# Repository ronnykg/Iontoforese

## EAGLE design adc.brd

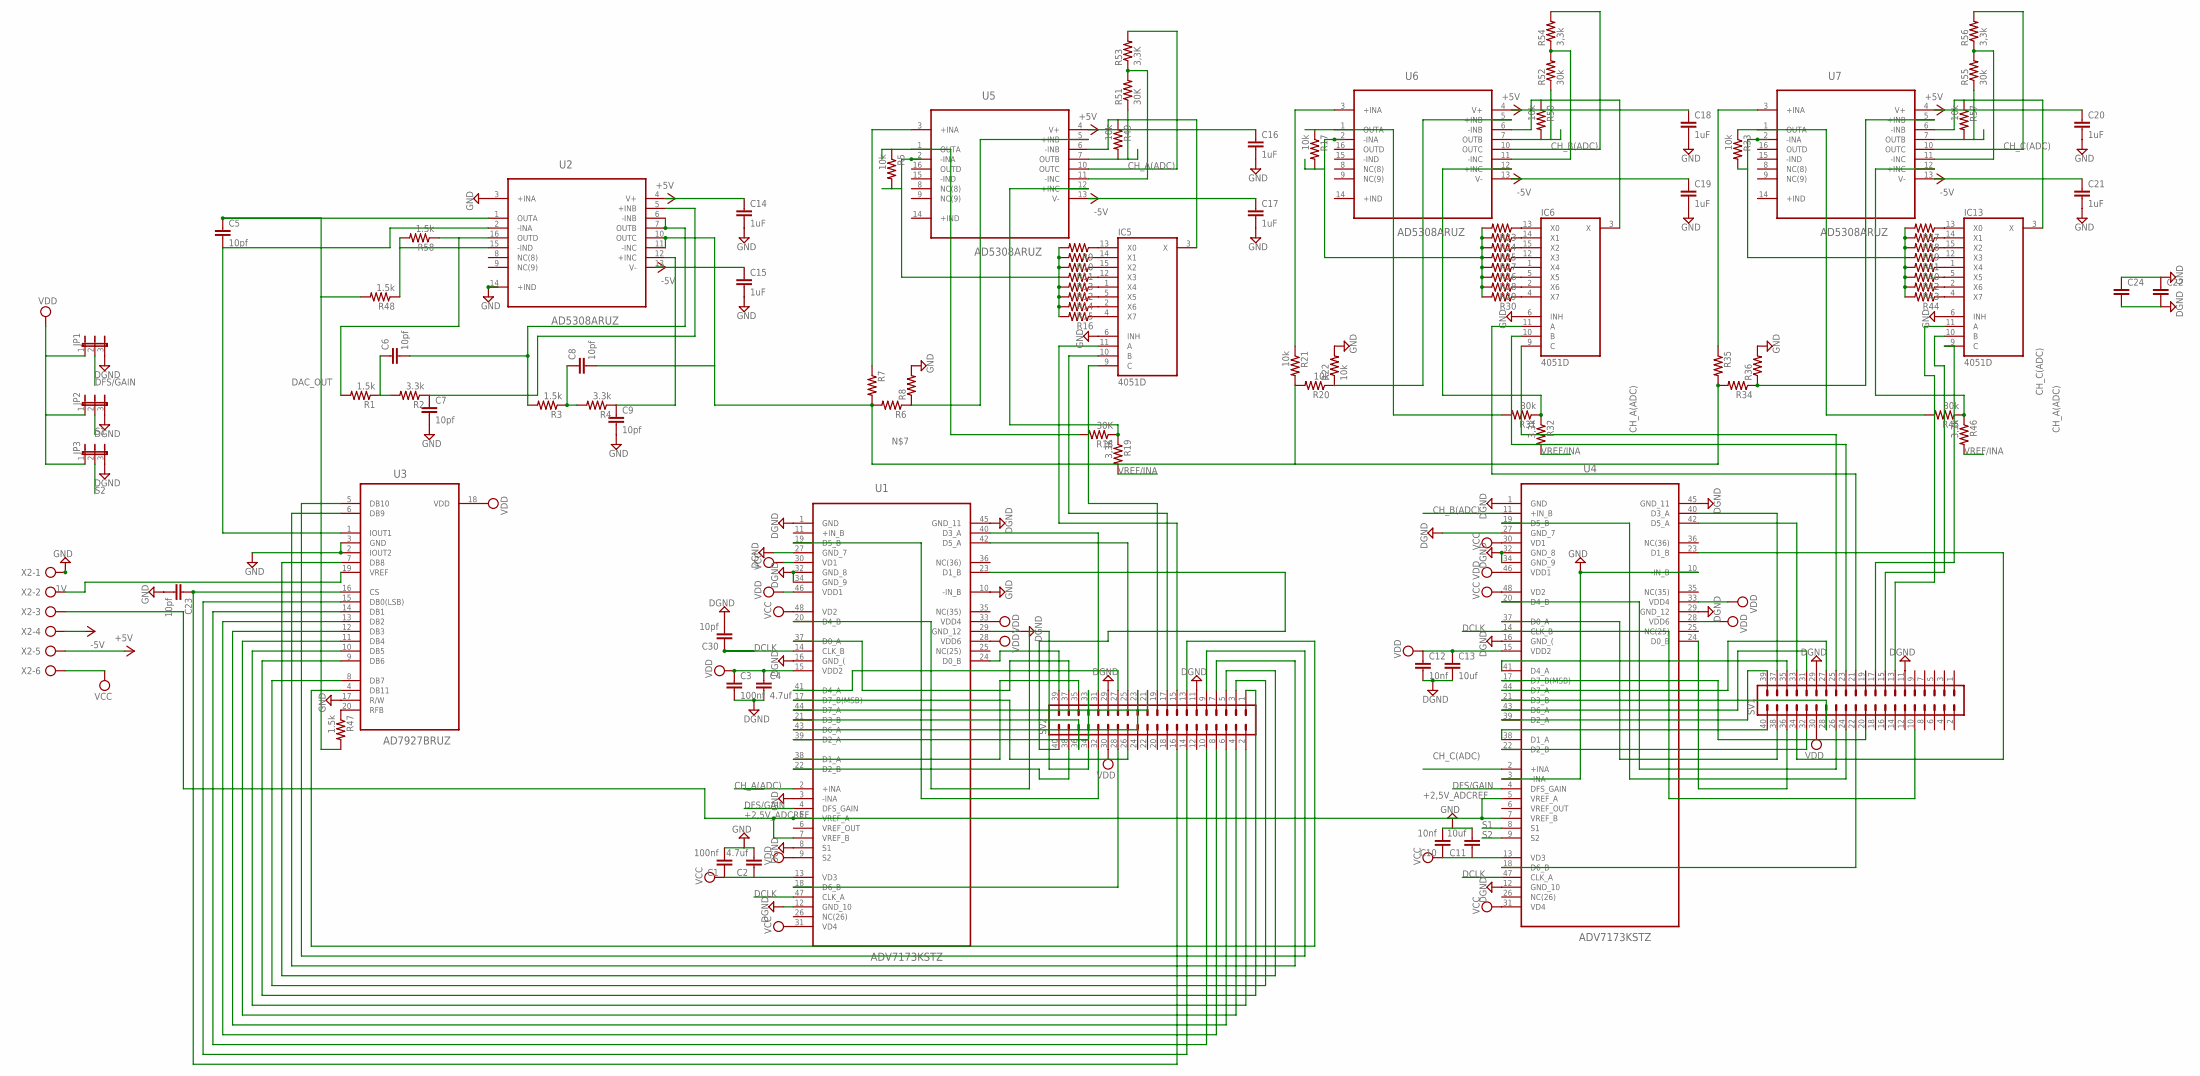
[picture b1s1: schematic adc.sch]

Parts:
C1, C3: 100nf; C0603
C2, C4: 4.7uf; C0603
C5, C6, C7, C8, C9, C23, C30: 10pf; C0603
C10, C12: 10nf; C0603
C11, C13: 10uf; C0603
C14, C15, C16, C17, C18, C19, C20, C21: 1uF; C0603
C22: C2,5-3; C2.5-3
C24: C10/6; C10B6
IC5, IC6, IC13: 4051D; SO16
JP1, JP2, JP3: JP2E; JP2
R1, R3, R47, R48, R58: 1.5k; 0603
R2, R4: 3.3k; 0603
R5, R17, R20, R21, R22, R33, R49, R50, R57: 10k; 0603
R6, R7, R8, R9, R10, R11, R12, R13, R14, R15, R16, R23, R24, R25, R26, R27, R28, R29, R30, R34, R35, R36, R37, R38, R39, R40, R41, R42, R43, R44: RESISTOR0603; 0603
R18, R51: 30K; 0603
R19, R53: 3,3K; 0603
R31, R45, R52, R55: 30k; 0603
R32, R46, R54, R56: 3,3k; 0603
SV1, SV2: MA20-2
U1, U4: ADV7173KSTZ; QFP50P900X900X160-48N
U2, U5, U6, U7: AD5308ARUZ; SOP65P640X120-16N
U3: AD7927BRUZ; SOP65P640X120-20N
X2: AK300/6

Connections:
1V: U3.19 (VREF), X2.2
+2,5V_ADCREF: U1.5 (VREF_A), U1.7 (VREF_B), U4.5 (VREF_A), U4.7 (VREF_B), X2.3
+5V: C14.1, C16.1, C18.1, C20.1, IC5.16 (+5V), IC6.16 (+5V), IC13.16 (+5V), U2.4 (V+), U5.4 (V+), U6.4 (V+), U7.4 (V+), X2.5
+IN_B: U1.11 (+IN_B)
-5V: C15.1, C17.1, C19.1, C21.1, IC5.7 (VEE), IC6.7 (VEE), IC13.7 (VEE), U2.13 (V-), U5.13 (V-), U6.13 (V-), U7.13 (V-), X2.4
CH_A(ADC): R53.2, U1.2 (+INA), U5.10 (OUTC)
CH_B(ADC): R54.2, U4.11 (+IN_B), U6.10 (OUTC)
CH_C(ADC): R56.2, U4.2 (+INA), U7.10 (OUTC)
DAC_OUT: C5.1, R47.2, R48.2, U2.1 (OUTA)
DCLK: C30.1, SV1.10, U1.14 (CLK_B), U1.47 (CLK_A), U4.14 (CLK_B), U4.47 (CLK_A)
DFS/GAIN: JP1.2, U1.4 (DFS_GAIN), U4.4 (DFS_GAIN)
DGND: C3.2, C4.2, C12.2, C13.2, C22.2, C24.2, C30.2, JP1.3, JP2.3, JP3.3, SV1.11, SV1.29, SV2.11, SV2.29, U1.1 (GND), U1.8 (S1), U1.12 (GND_10), U1.16 (GND_(), U1.27 (GND_7), U1.29 (GND_12), U1.32 (GND_8), U1.34 (GND_9), U1.45 (GND_11), U4.1 (GND), U4.12 (GND_10), U4.16 (GND_(), U4.27 (GND_7), U4.29 (GND_12), U4.32 (GND_8), U4.34 (GND_9), U4.45 (GND_11)
GND: C1.2, C2.2, C7.2, C9.2, C10.2, C11.2, C14.2, C15.2, C16.2, C17.2, C18.2, C19.2, C20.2, C21.2, C22.1, C23.2, C24.1, IC5.6 (INH), IC5.8 (GND), IC6.6 (INH), IC6.8 (GND), IC13.6 (INH), IC13.8 (GND), R8.2, R22.2, R36.2, U1.3 (-INA), U1.10 (-IN_B), U2.3 (+INA), U2.14 (+IND), U3.2 (IOUT2), U3.3 (GND), U3.17 (R/W), U4.3 (-INA), U4.10 (-IN_B), X2.1
unnamed: C7.1, R2.1, U2.5 (+INB)
unnamed: C6.1, R1.1, R2.2
unnamed: R48.1, R58.2, U2.15 (-IND)
unnamed: C6.2, R3.2, U2.6 (-INB), U2.7 (OUTB)
unnamed: C9.1, R4.1, U2.12 (+INC)
unnamed: C8.1, R3.1, R4.2
unnamed: C8.2, R6.2, R7.2, R20.2, R21.2, R34.2, R35.2, U2.10 (OUTC), U2.11 (-INC)
unnamed: SV2.31, U1.40 (D3_A)
unnamed: SV2.25, U1.42 (D5_A)
unnamed: SV2.39, U1.24 (D0_B)
unnamed: SV2.32, U1.19 (D5_B)
unnamed: SV2.34, U1.20 (D4_B)
unnamed: SV2.37, U1.37 (D0_A)
unnamed: SV2.27, U1.41 (D4_A)
unnamed: SV2.21, U1.44 (D7_A)
unnamed: SV2.36, U1.21 (D3_B)
unnamed: SV2.23, U1.43 (D6_A)
unnamed: SV2.33, U1.39 (D2_A)
unnamed: SV2.35, U1.38 (D1_A)
unnamed: SV2.38, U1.22 (D2_B)
unnamed: SV2.28, U1.18 (D6_B)
unnamed: SV2.26, U1.17 (D7_B(MSB))
unnamed: SV2.13, U3.4 (DB11)
unnamed: SV2.40, U1.23 (D1_B)
unnamed: SV2.9, U3.5 (DB10)
unnamed: SV2.7, U3.6 (DB9)
unnamed: SV2.5, U3.7 (DB8)
unnamed: SV2.3, U3.8 (DB7)
unnamed: SV2.1, U3.9 (DB6)
unnamed: SV2.2, U3.10 (DB5)
unnamed: SV2.4, U3.11 (DB4)
unnamed: SV2.6, U3.12 (DB3)
unnamed: SV2.8, U3.13 (DB2)
unnamed: SV2.10, U3.14 (DB1)
unnamed: SV2.14, U3.15 (DB0(LSB))
unnamed: SV1.38, U4.37 (D0_A)
unnamed: IC5.13 (X0), R9.1
unnamed: IC5.14 (X1), R10.1
unnamed: IC5.15 (X2), R11.1
unnamed: IC5.1 (X4), R12.1
unnamed: IC5.12 (X3), R13.1
unnamed: IC5.5 (X5), R14.1
unnamed: IC5.2 (X6), R15.1
unnamed: IC5.4 (X7), R16.1
unnamed: IC6.13 (X0), R23.1
unnamed: IC6.14 (X1), R24.1
unnamed: R17.2, R23.2, R24.2, R25.2, R26.2, R27.2, R28.2, R29.2, R30.2, U6.2 (-INA)
unnamed: R5.2, R9.2, R10.2, R11.2, R12.2, R13.2, R14.2, R15.2, R16.2, U5.2 (-INA)
unnamed: R18.1, R19.1, U5.12 (+INC)
unnamed: R49.2, R51.1, U5.7 (OUTB)
unnamed: IC6.15 (X2), R25.1
unnamed: IC6.1 (X4), R26.1
unnamed: IC6.12 (X3), R27.1
unnamed: IC6.5 (X5), R28.1
unnamed: IC6.2 (X6), R29.1
unnamed: IC6.4 (X7), R30.1
unnamed: R52.2, R54.1, U6.11 (-INC)
unnamed: R33.1, R45.2, U7.1 (OUTA)
unnamed: IC13.3 (X), R57.1, U7.6 (-INB)
unnamed: IC13.13 (X0), R37.1
unnamed: IC13.14 (X1), R38.1
unnamed: IC13.15 (X2), R39.1
unnamed: IC13.1 (X4), R40.1
unnamed: IC13.12 (X3), R41.1
unnamed: IC13.5 (X5), R42.1
unnamed: IC13.2 (X6), R43.1
unnamed: IC13.4 (X7), R44.1
unnamed: R34.1, R36.1, U7.5 (+INB)
unnamed: R6.1, R8.1, U5.5 (+INB)
unnamed: R20.1, R22.1, U6.5 (+INB)
unnamed: R7.1, U5.3 (+INA)
unnamed: SV1.40, U4.38 (D1_A)
unnamed: SV1.39, U4.39 (D2_A)
unnamed: SV1.36, U4.24 (D0_B)
unnamed: SV1.24, U4.19 (D5_B)
unnamed: SV1.26, U4.20 (D4_B)
unnamed: SV1.37, U4.40 (D3_A)
unnamed: SV1.35, U4.41 (D4_A)
unnamed: SV1.33, U4.42 (D5_A)
unnamed: SV1.28, U4.21 (D3_B)
unnamed: SV1.31, U4.43 (D6_A)
unnamed: SV1.27, U4.44 (D7_A)
unnamed: SV1.32, U4.22 (D2_B)
unnamed: SV1.22, U4.18 (D6_B)
unnamed: SV1.20, U4.17 (D7_B(MSB))
unnamed: SV1.34, U4.23 (D1_B)
unnamed: IC5.9 (C), SV2.19
unnamed: IC5.10 (B), SV2.17
unnamed: IC13.9 (C), SV1.17
unnamed: IC13.10 (B), SV1.15
unnamed: IC13.11 (A), SV1.13
unnamed: IC6.9 (C), SV1.25
unnamed: IC6.10 (B), SV1.23
unnamed: IC6.11 (A), SV1.21
unnamed: IC5.3 (X), R49.1, U5.6 (-INB)
unnamed: R31.1, R32.1, U6.12 (+INC)
unnamed: R33.2, R37.2, R38.2, R39.2, R40.2, R41.2, R42.2, R43.2, R44.2, U7.2 (-INA)
unnamed: C5.2, U2.2 (-INA), U3.1 (IOUT1)
unnamed: R45.1, R46.1, U7.12 (+INC)
unnamed: R5.1, R18.2, U5.1 (OUTA)
unnamed: R35.1, U7.3 (+INA)
unnamed: R21.1, U6.3 (+INA)
unnamed: R47.1, U3.20 (RFB)
unnamed: IC5.11 (A), SV2.15
unnamed: C23.1, SV2.16, U3.16 (CS)
unnamed: R55.2, R56.1, U7.11 (-INC)
unnamed: R51.2, R53.1, U5.11 (-INC)
unnamed: R55.1, R57.2, U7.7 (OUTB)
unnamed: R17.1, R31.2, U6.1 (OUTA)
unnamed: R50.2, R52.1, U6.7 (OUTB)
unnamed: IC6.3 (X), R50.1, U6.6 (-INB)
unnamed: R1.2, R58.1, U2.16 (OUTD)
S1: JP2.2, U4.8 (S1)
S2: JP3.2, U4.9 (S2)
VCC: C1.1, C2.1, C10.1, C11.1, U1.13 (VD3), U1.30 (VD1), U1.31 (VD4), U1.48 (VD2), U4.13 (VD3), U4.30 (VD1), U4.31 (VD4), U4.48 (VD2), X2.6
VDD: C3.1, C4.1, C12.1, C13.1, JP1.1, JP2.1, JP3.1, SV1.30, SV2.30, U1.9 (S2), U1.15 (VDD2), U1.28 (VDD6), U1.33 (VDD4), U1.46 (VDD1), U3.18 (VDD), U4.15 (VDD2), U4.28 (VDD6), U4.33 (VDD4), U4.46 (VDD1)
VEE: IC5.7 (VEE), IC6.7 (VEE), IC13.7 (VEE)
VREF/INA: R19.2, R32.2, R46.2

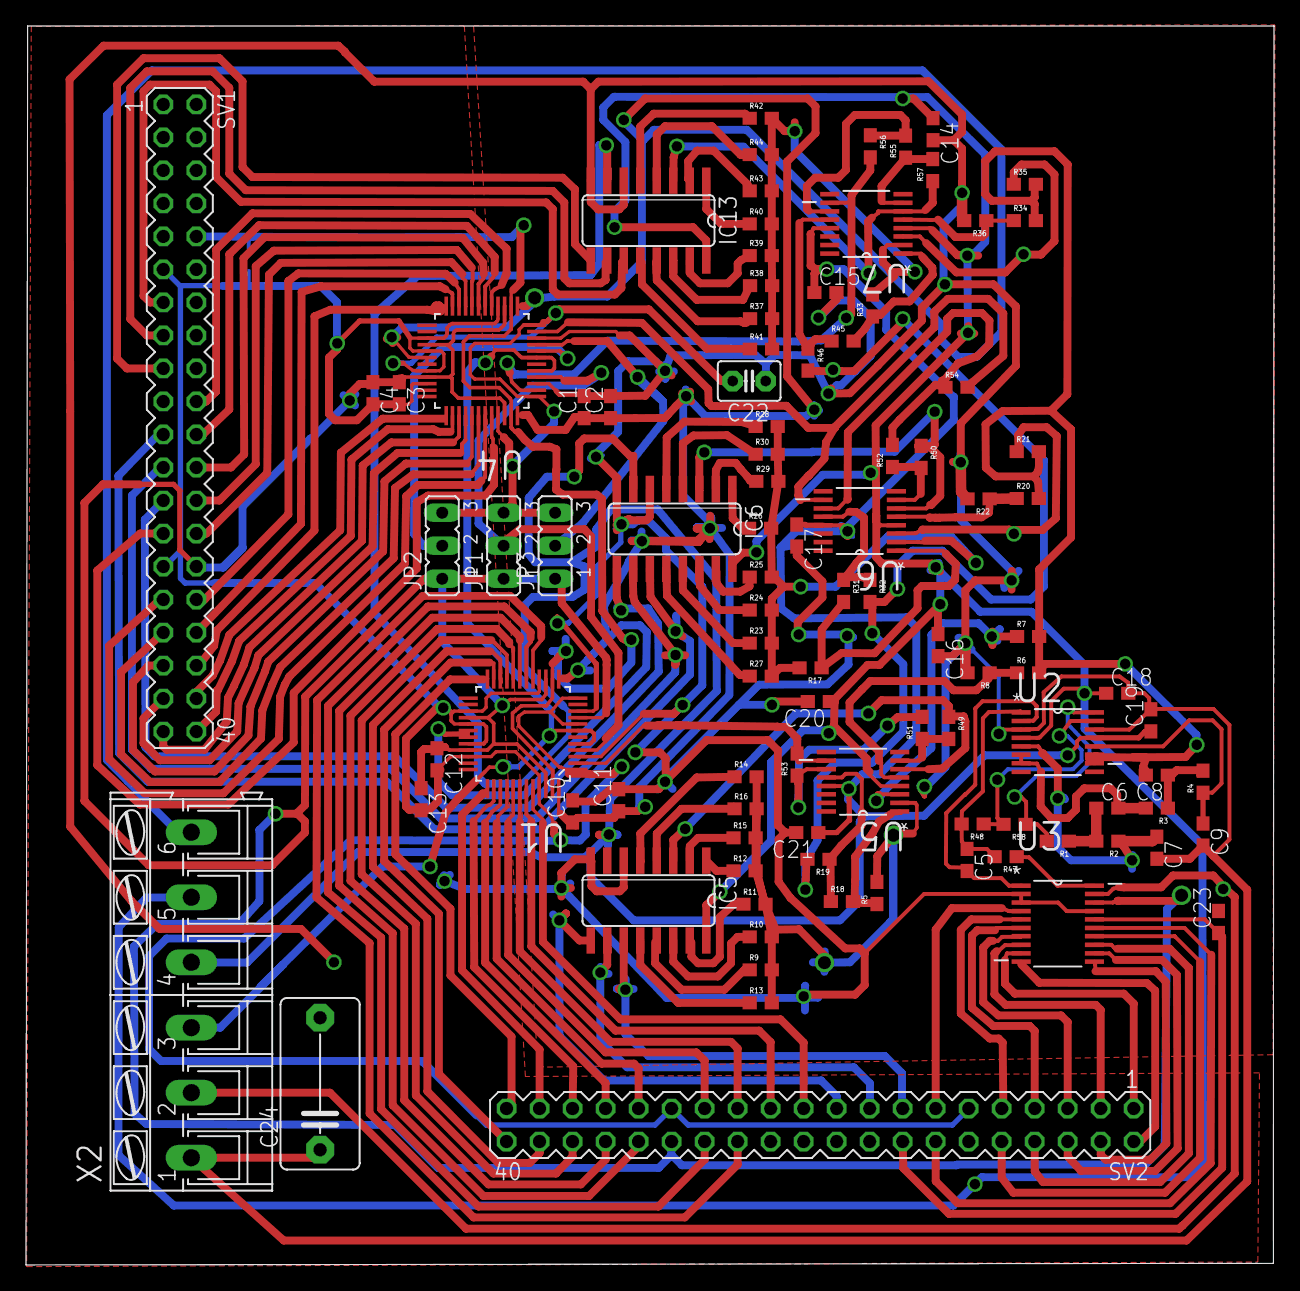
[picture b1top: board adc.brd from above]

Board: 2 copper layers, 96.0 x 95.3 mm, 99 parts (1 on the bottom side), 130 nets.

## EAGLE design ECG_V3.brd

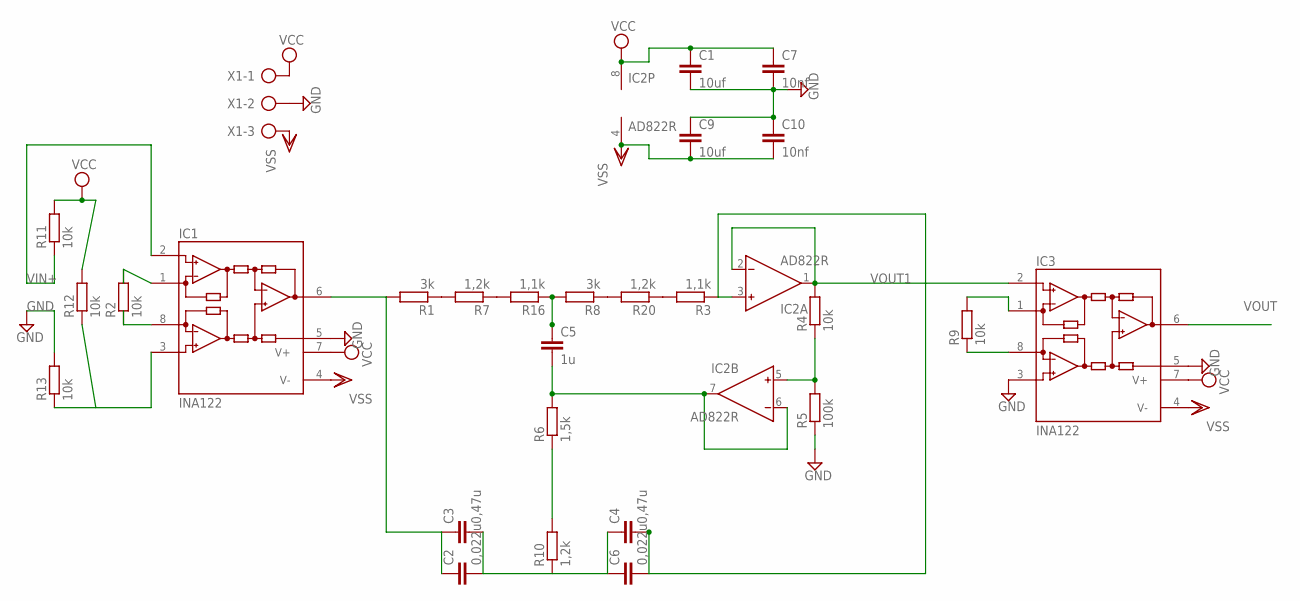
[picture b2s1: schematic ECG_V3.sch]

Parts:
C1, C9: 10uf; C0603
C2, C6: 0,022u; C0603
C3, C4: 0,47u; C0603
C5: 1u; C0603
C7, C10: 10nf; C0603
IC1, IC3: INA122; SO08
IC2: AD822R; SO8
R1, R8: 3k; R0603
R2, R4, R9, R11, R12, R13: 10k; R0603
R3, R16: 1,1k; R0603
R5: 100k; R0603
R6: 1,5k; R0603
R7, R10, R20: 1,2k; R0603
X1: AK300/3

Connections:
GND: C1.2, C7.2, C9.1, C10.1, IC1.5 (REF), IC3.3 (+IN), IC3.5 (REF), R5.1, R13.2, X1.2
unnamed: IC3.1 (RG), R9.2
unnamed: IC3.8 (RG), R9.1
unnamed: IC1.1 (RG), R2.2
unnamed: IC1.8 (RG), R2.1
unnamed: R1.1, R7.2
unnamed: R7.1, R16.2
unnamed: R3.2, R20.1
unnamed: IC2.5 (IN+), R4.1, R5.2
unnamed: R8.1, R20.2
unnamed: C5.2, IC2.6 (IN-), IC2.7 (OUT), R6.2
unnamed: C5.1, R8.2, R16.1
unnamed: IC1.3 (+IN), R12.1, R13.1
unnamed: R6.1, R10.2
unnamed: C2.2, C3.2, C4.1, C6.1, R10.1
unnamed: C2.1, C3.1, IC1.6 (OUT), R1.2
unnamed: C4.2, C6.2, IC2.3 (IN+), R3.1
VCC: C1.1, C7.1, IC1.7 (V+), IC2.8 (V+), IC3.7 (V+), R11.2, R12.2, X1.1
VIN+: IC1.2 (-IN), R11.1
VOUT: IC3.6 (OUT)
VOUT1: IC2.1 (OUT), IC2.2 (IN-), IC3.2 (-IN), R4.2
VSS: C9.2, C10.2, IC1.4 (V-), IC2.4 (V-), IC3.4 (V-), X1.3

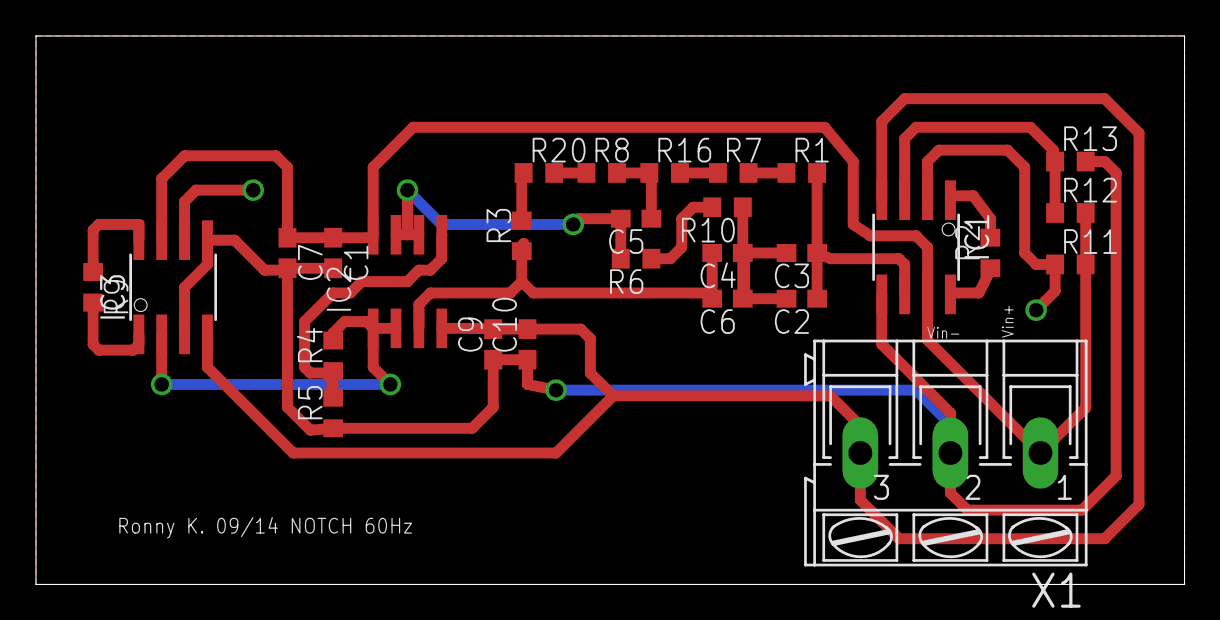
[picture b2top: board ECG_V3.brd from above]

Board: 2 copper layers, 63.8 x 30.5 mm, 28 parts (0 on the bottom side), 21 nets.

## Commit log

2015-06-15 :circus_tent: Added .gitattributes
2015-06-15 Repositório 2
    Adicionado quase todos os arquivos, ignorado .bak .wav
2015-07-07 Updade 1V ADC.brd enviada pra digikart
2015-11-18 atualização
    FPGA - send ADC
    C# - DFT
    Placa - 2 grounds
2016-02-25 Atualização
2016-05-03 atualização de dados
2016-05-09 Dados
2016-08-24 new data
